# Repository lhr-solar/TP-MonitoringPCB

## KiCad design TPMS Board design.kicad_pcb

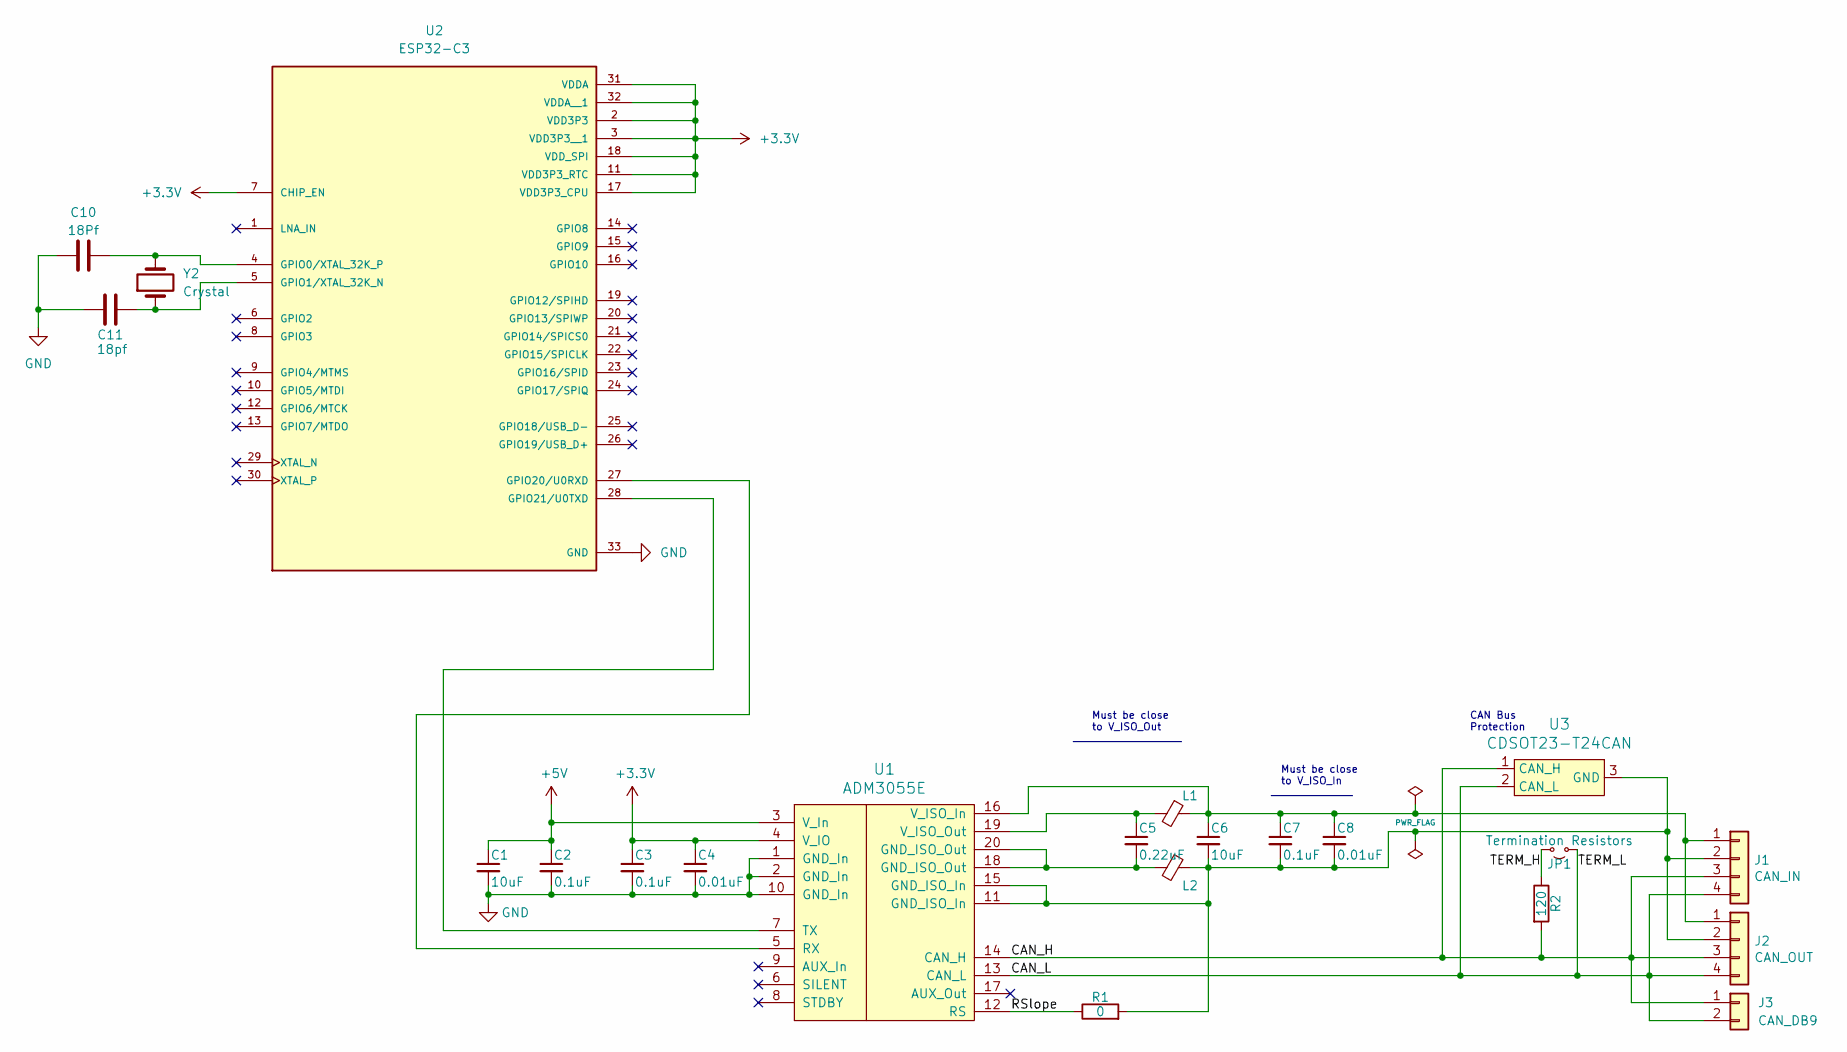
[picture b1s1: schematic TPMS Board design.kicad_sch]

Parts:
C1, C6: 10uF; C_0805_2012Metric; Mouser Part Number 963-TMK212BBJ106MGHT
C2, C3, C7: 0.1uF; C_0805_2012Metric; Mouser Part Number 80-C0805C104M5R
C4, C8: 0.01uF; C_0805_2012Metric
C5: 0.22uF; C_0805_2012Metric; Mouser Part Number 80-C0805C224J1RECTU
C10: 18Pf; C_0805_2012Metric
C11: 18pf; C_0805_2012Metric
J1: CAN_IN; Molex_MicroFit3.0_1x4xP3.00mm_PolarizingPeg_Vertical
J2: CAN_OUT; Molex_MicroFit3.0_1x4xP3.00mm_PolarizingPeg_Vertical
J3: CAN_DB9; Molex_Micro-Fit_3.0_43650-0215_1x02_P3.00mm_Vertical
JP1: Termination Resistors; PinHeader_1x02_P2.54mm_Vertical
L1, L2: 1.8k; L_0805_2012Metric; Mouser Part Number 710-742792090
R1: 0; R_0805_2012Metric; Mouser Part Number 71-CRCW08050000Z0EAC
R2: 120; R_0805_2012Metric
U1: ADM3055E; SOIC-20W_7.5x15.4mm_Pitch1.27mm
U2: ESP32-C3; QFN32_5X5_EXP; PARTREV 2.0
U3: CDSOT23-T24CAN; SOT-23-3; Mouser Part Number 652-CDSOT23-T24CAN
Y2: Crystal; Crystal_SMD_TXC_7A-2Pin_5x3.2mm

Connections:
+3.3V: C3.1, C4.1, U1.4 (V_IO), U2.2 (VDD3P3), U2.3 (VDD3P3__1), U2.7 (CHIP_EN), U2.11 (VDD3P3_RTC), U2.17 (VDD3P3_CPU), U2.18 (VDD_SPI), U2.31 (VDDA), U2.32 (VDDA__1)
+5V: C1.1, C2.1, U1.3 (V_In)
/CAN_H: J1.3, J2.3, J3.1, R2.2, U1.14 (CAN_H), U3.1 (CAN_H)
/CAN_L: J1.4, J2.4, J3.2, JP1.1 (A), U1.13 (CAN_L), U3.2 (CAN_L)
/RSlope: R1.1, U1.12 (RS)
/TERM_H: JP1.2 (B), R2.1
GND: C1.2, C2.2, C3.2, C4.2, C10.1, C11.1, U1.1 (GND_In), U1.2 (GND_In), U1.10 (GND_In), U2.33 (GND)
unnamed: C5.2, L2.2, U1.18 (GND_ISO_Out), U1.20 (GND_ISO_Out)
unnamed: C6.1, C7.1, C8.1, J1.1, J2.1, L1.1, U1.16 (V_ISO_In)
unnamed: C6.2, C7.2, C8.2, J1.2, J2.2, L2.1, R1.2, U1.11 (GND_ISO_In), U1.15 (GND_ISO_In), U3.3 (GND)
unnamed: U1.5 (RX), U2.27 (GPIO20/U0RXD)
unnamed: U1.7 (TX), U2.28 (GPIO21/U0TXD)
unnamed: C5.1, L1.2, U1.19 (V_ISO_Out)
unnamed: C10.2, U2.4 (GPIO0/XTAL_32K_P), Y2.2
unnamed: C11.2, U2.5 (GPIO1/XTAL_32K_N), Y2.1

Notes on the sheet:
Must be close to V_ISO_Out
CAN Bus Protection
Must be close to V_ISO_In

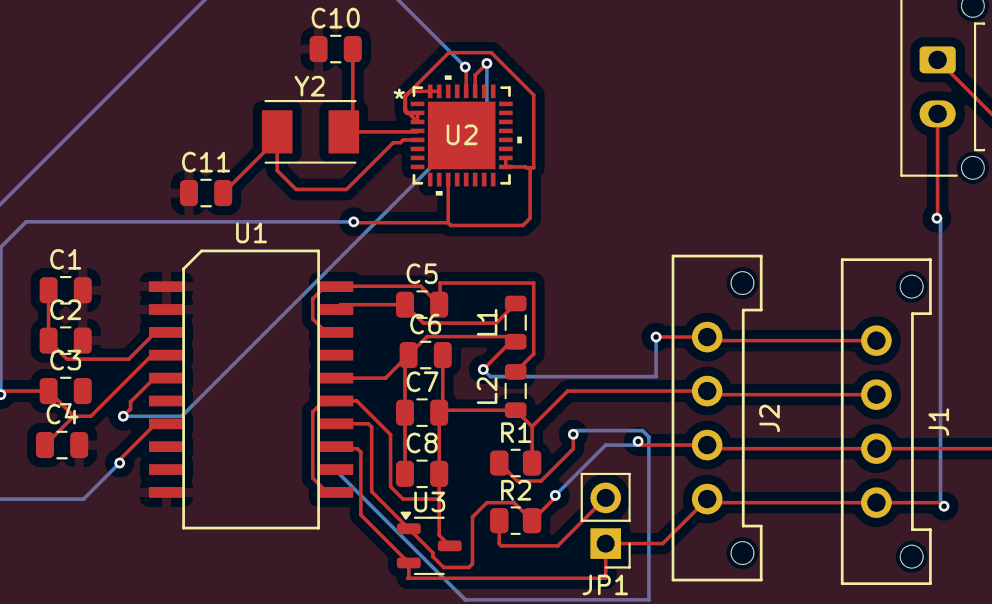
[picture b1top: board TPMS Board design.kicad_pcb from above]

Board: 2 copper layers, 22 parts (0 on the bottom side), 15 nets.

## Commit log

2025-05-09 First Upload
2025-06-18 moved two capacitors
